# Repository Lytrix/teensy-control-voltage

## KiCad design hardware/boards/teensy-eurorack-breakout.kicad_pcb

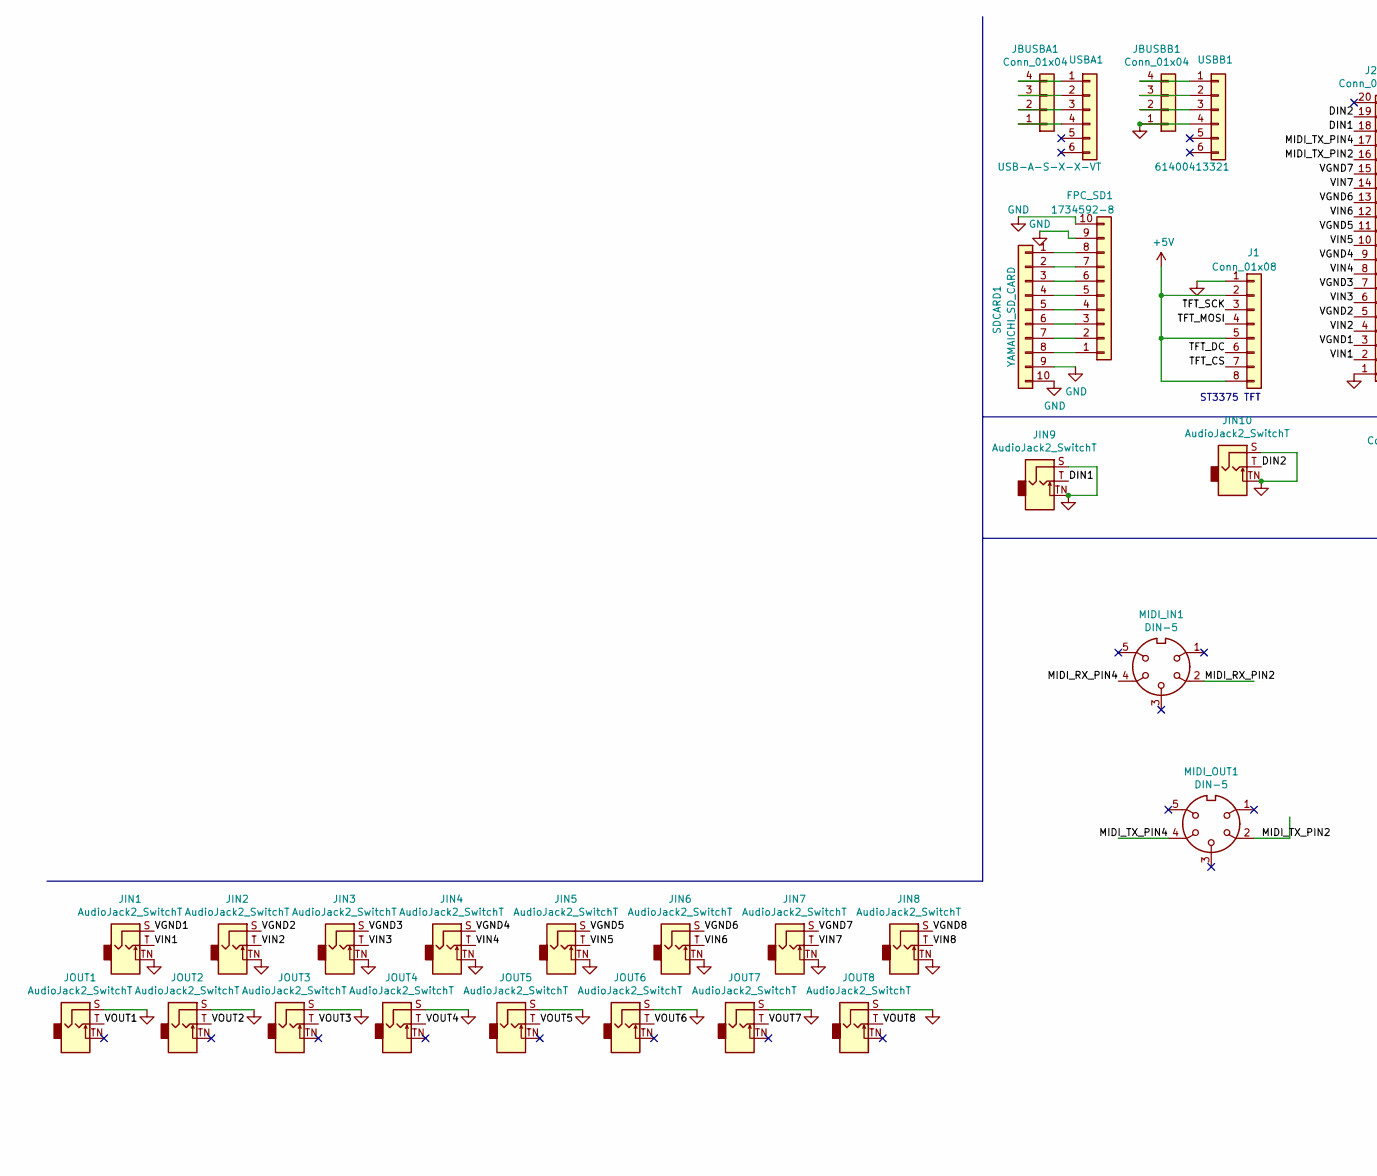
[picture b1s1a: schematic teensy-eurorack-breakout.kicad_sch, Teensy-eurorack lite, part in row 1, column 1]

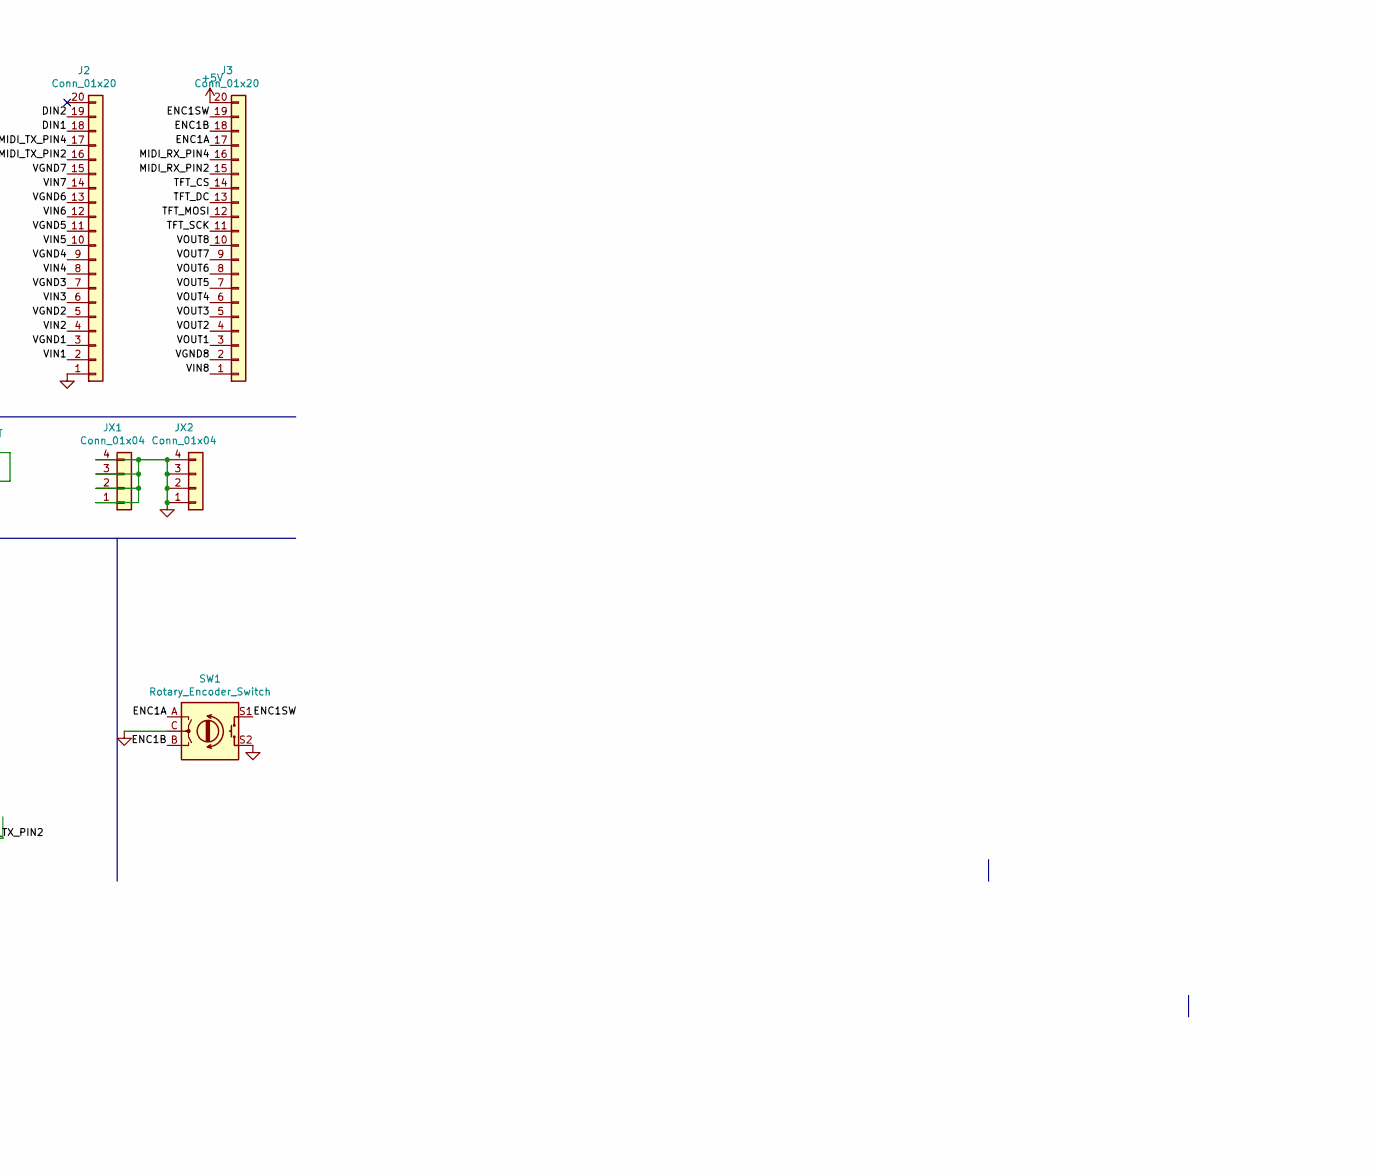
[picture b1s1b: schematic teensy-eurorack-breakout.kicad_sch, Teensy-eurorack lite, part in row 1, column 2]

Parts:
FPC_SD1: 1734592-8; HFW8R-1STE1LF
J1: Conn_01x08; ST7735
J2, J3: Conn_01x20; PinSocket_1x20_P2.54mm_Vertical
JBUSBA1: Conn_01x04; PinSocket_1x04_P2.54mm_Vertical
JBUSBB1: Conn_01x04; PinSocket_1x04_P2.54mm_Vertical
JIN1, JIN2, JIN3, JIN4, JIN5, JIN6, JIN7, JIN8, JIN9, JIN10: AudioJack2_SwitchT; WQP-PJ301M-12_JACK
JOUT1, JOUT2, JOUT3, JOUT4, JOUT5, JOUT6, JOUT7, JOUT8: AudioJack2_SwitchT; WQP-PJ301M-12_JACK
JX1, JX2: Conn_01x04; PinSocket_1x04_P2.54mm_Vertical
MIDI_IN1: DIN-5; OG-MIDI_SD-50BV
MIDI_OUT1: DIN-5; OG-MIDI_SD-50BV
SDCARD1: YAMAICHI_SD_CARD; YAMAICHI_MICROSD_VERTICAL
SW1: Rotary_Encoder_Switch; RotaryEncoder_Alps_EC12E-Switch_Vertical_H20mm_CircularMoun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
USBA1: USB-A-S-X-X-VT
USBB1: 61400413321; WURTH_ELECTRONICS_61400413321_0

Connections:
+5V: J1.2, J1.5, J1.8, J3.20
/DIN1: J2.18, JIN9.T
/DIN2: J2.19, JIN10.T
/ENC1A: J3.17, SW1.A
/ENC1B: J3.18, SW1.B
/ENC1SW: J3.19, SW1.S1
/MIDI_RX_PIN2: J3.15, MIDI_IN1.2
/MIDI_RX_PIN4: J3.16, MIDI_IN1.4
/MIDI_TX_PIN2: J2.16, MIDI_OUT1.2
/MIDI_TX_PIN4: J2.17, MIDI_OUT1.4
/TFT_CS: J1.7, J3.14
/TFT_DC: J1.6, J3.13
/TFT_MOSI: J1.4, J3.12
/TFT_SCK: J1.3, J3.11
/VGND1: J2.3, JIN1.S
/VGND2: J2.5, JIN2.S
/VGND3: J2.7, JIN3.S
/VGND4: J2.9, JIN4.S
/VGND5: J2.11, JIN5.S
/VGND6: J2.13, JIN6.S
/VGND7: J2.15, JIN7.S
/VGND8: J3.2, JIN8.S
/VIN1: J2.2, JIN1.T
/VIN2: J2.4, JIN2.T
/VIN3: J2.6, JIN3.T
/VIN4: J2.8, JIN4.T
/VIN5: J2.10, JIN5.T
/VIN6: J2.12, JIN6.T
/VIN7: J2.14, JIN7.T
/VIN8: J3.1, JIN8.T
/VOUT1: J3.3, JOUT1.T
/VOUT2: J3.4, JOUT2.T
/VOUT3: J3.5, JOUT3.T
/VOUT4: J3.6, JOUT4.T
/VOUT5: J3.7, JOUT5.T
/VOUT6: J3.8, JOUT6.T
/VOUT7: J3.9, JOUT7.T
/VOUT8: J3.10, JOUT8.T
GND: FPC_SD1.9, FPC_SD1.10, J1.1, J2.1, JBUSBB1.1, JIN1.TN, JIN2.TN, JIN3.TN, JIN4.TN, JIN5.TN, JIN6.TN, JIN7.TN, JIN8.TN, JIN9.S, JIN9.TN, JIN10.S, JIN10.TN, JOUT1.S, JOUT2.S, JOUT3.S, JOUT4.S, JOUT5.S, JOUT6.S, JOUT7.S, JOUT8.S, JX1.1, JX1.2, JX1.3, JX1.4, JX2.1, JX2.2, JX2.3, JX2.4, SDCARD1.9, SDCARD1.10, SW1.C, SW1.S2, USBB1.4
unnamed: FPC_SD1.1, SDCARD1.8
unnamed: FPC_SD1.2, SDCARD1.7
unnamed: FPC_SD1.3, SDCARD1.6
unnamed: FPC_SD1.4, SDCARD1.5
unnamed: FPC_SD1.5, SDCARD1.4
unnamed: FPC_SD1.6, SDCARD1.3
unnamed: FPC_SD1.7, SDCARD1.2
unnamed: FPC_SD1.8, SDCARD1.1
unnamed: JBUSBA1.1, USBA1.4
unnamed: JBUSBA1.2, USBA1.3
unnamed: JBUSBA1.3, USBA1.2
unnamed: JBUSBA1.4, USBA1.1
unnamed: JBUSBB1.2, USBB1.3
unnamed: JBUSBB1.3, USBB1.2
unnamed: JBUSBB1.4, USBB1.1

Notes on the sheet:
ST3375 TFT

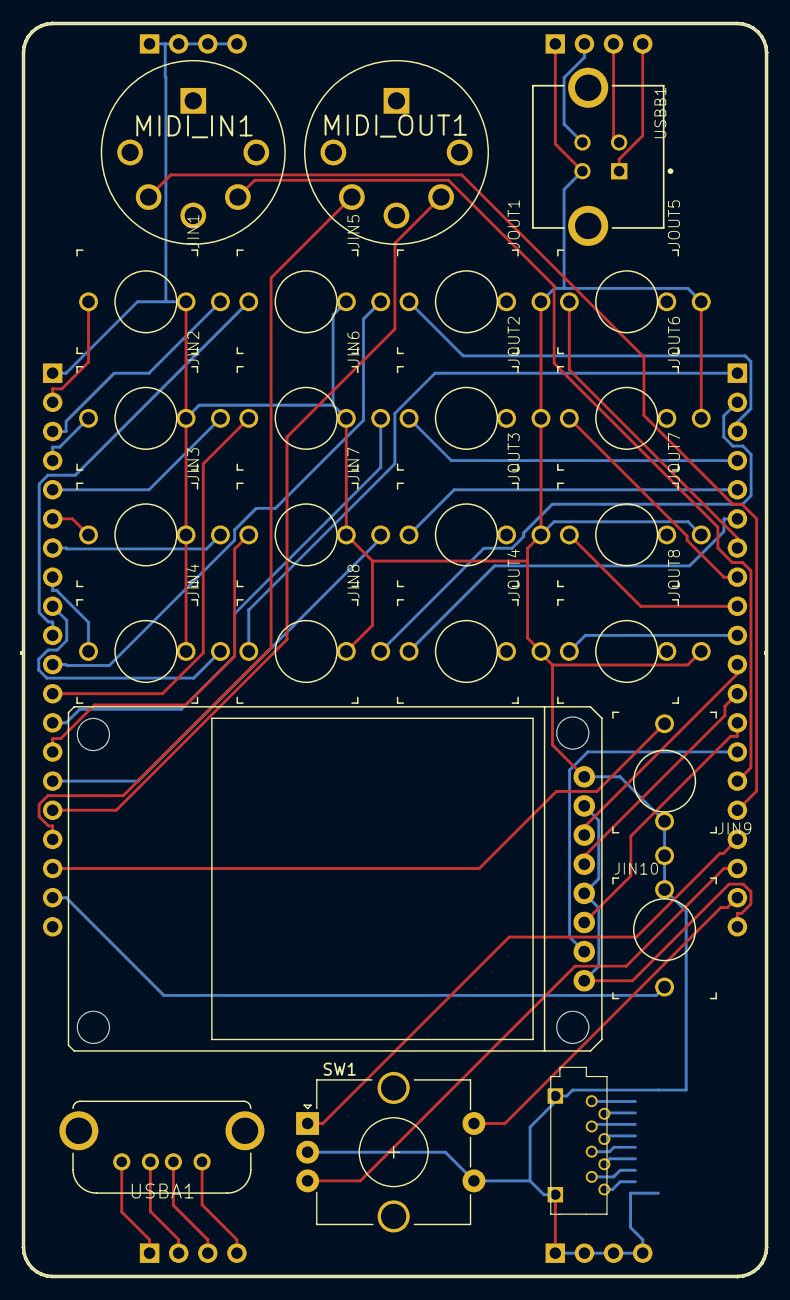
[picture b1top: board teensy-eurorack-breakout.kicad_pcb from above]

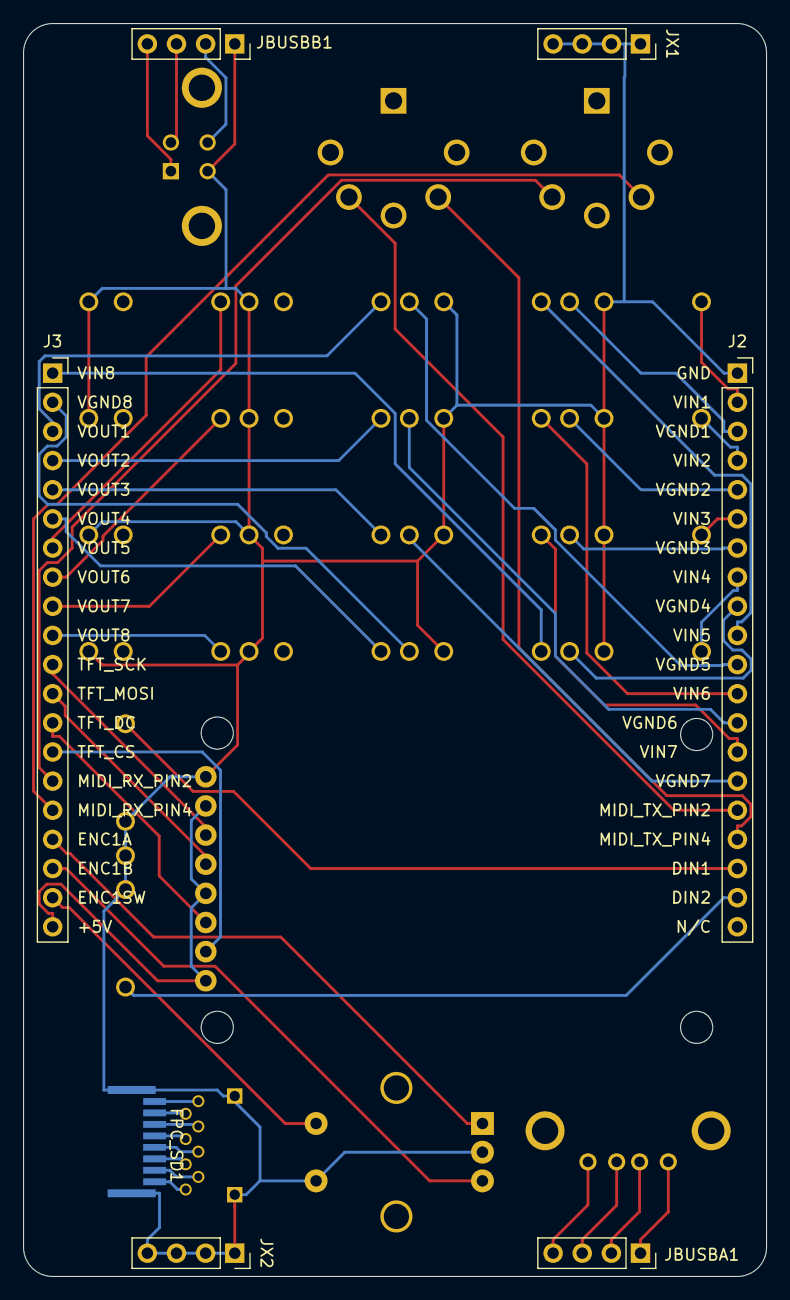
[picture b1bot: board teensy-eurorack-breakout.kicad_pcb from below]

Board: 2 copper layers, 64.8 x 109.2 mm, 32 parts (7 on the bottom side), 54 nets.

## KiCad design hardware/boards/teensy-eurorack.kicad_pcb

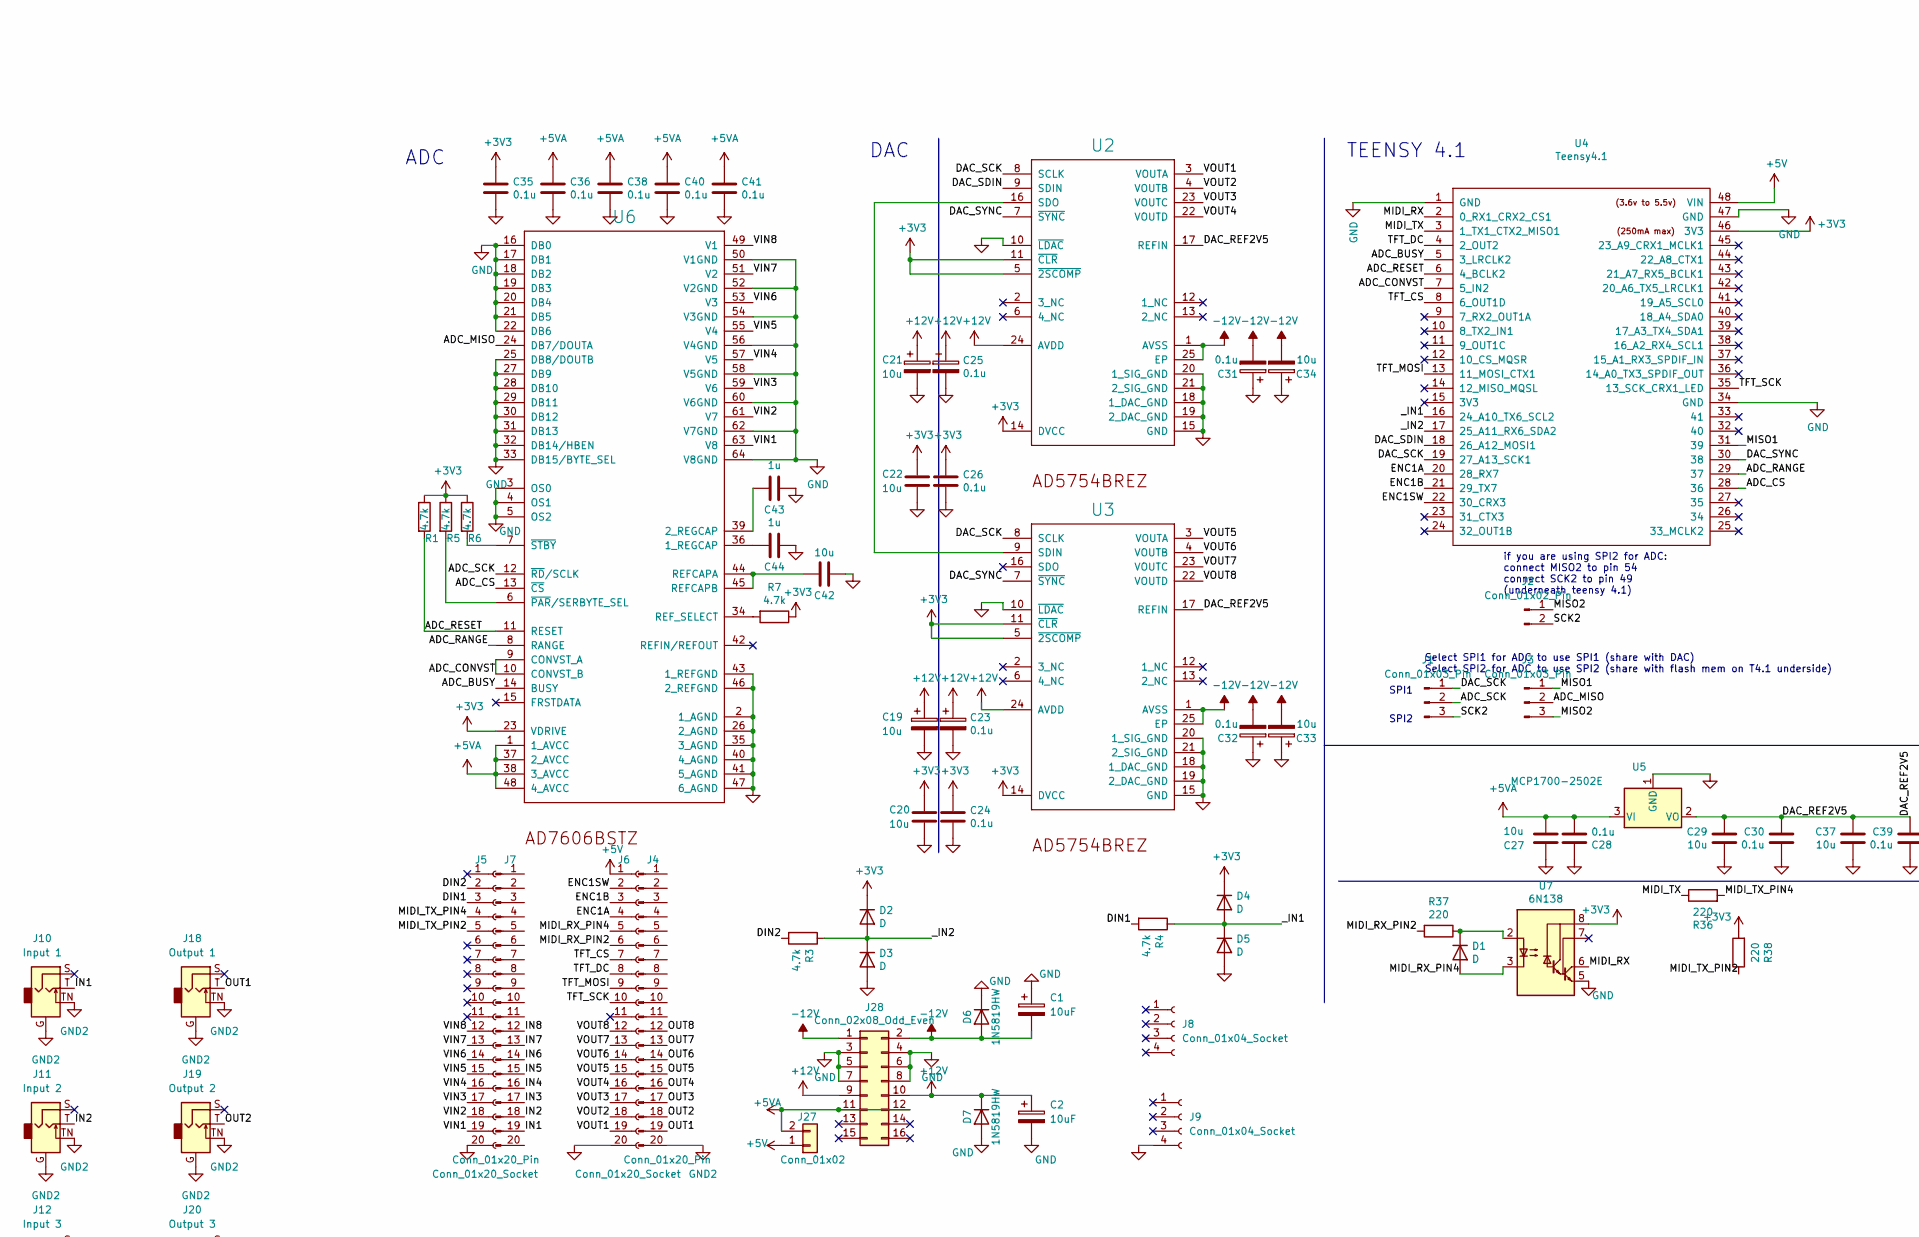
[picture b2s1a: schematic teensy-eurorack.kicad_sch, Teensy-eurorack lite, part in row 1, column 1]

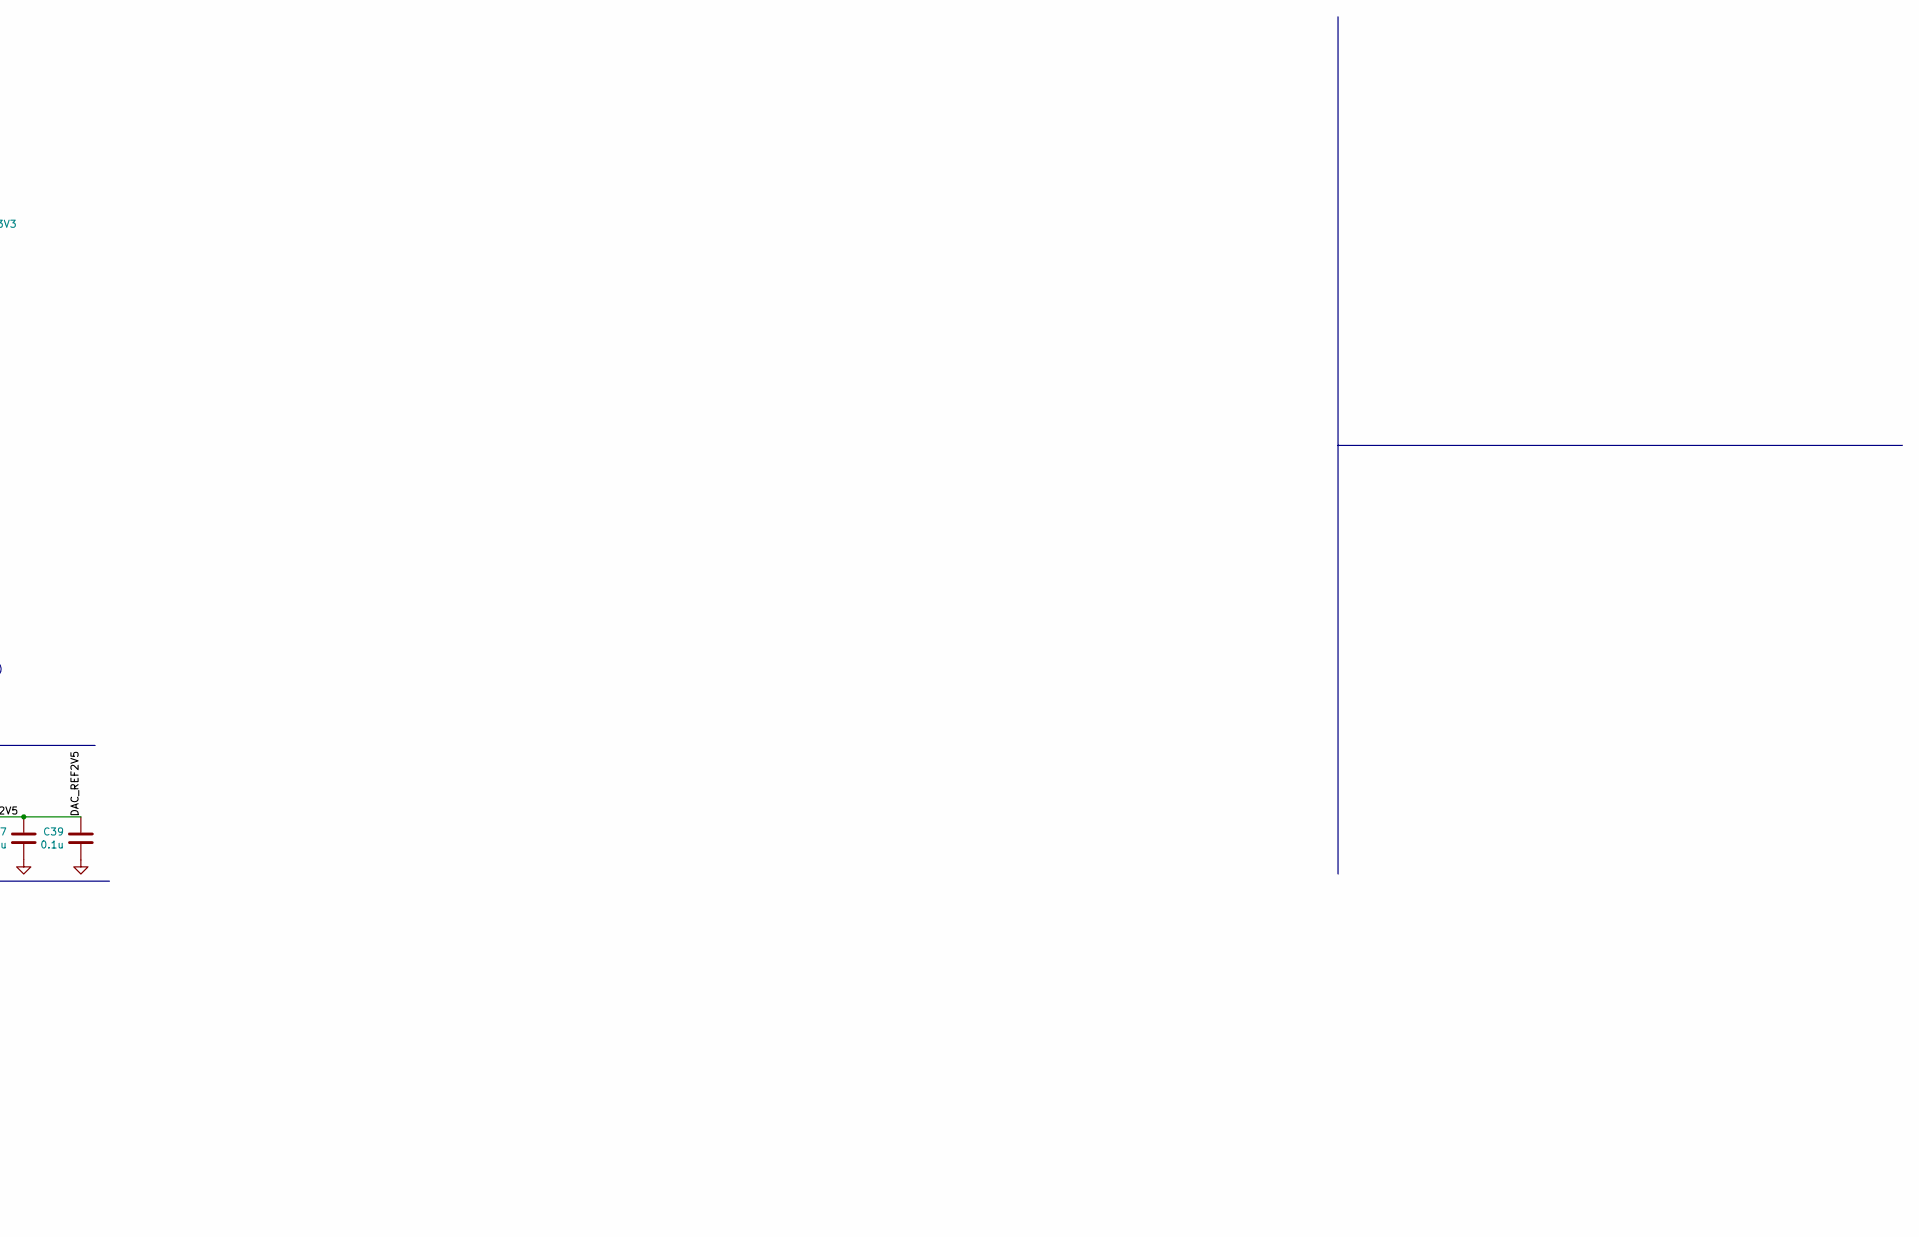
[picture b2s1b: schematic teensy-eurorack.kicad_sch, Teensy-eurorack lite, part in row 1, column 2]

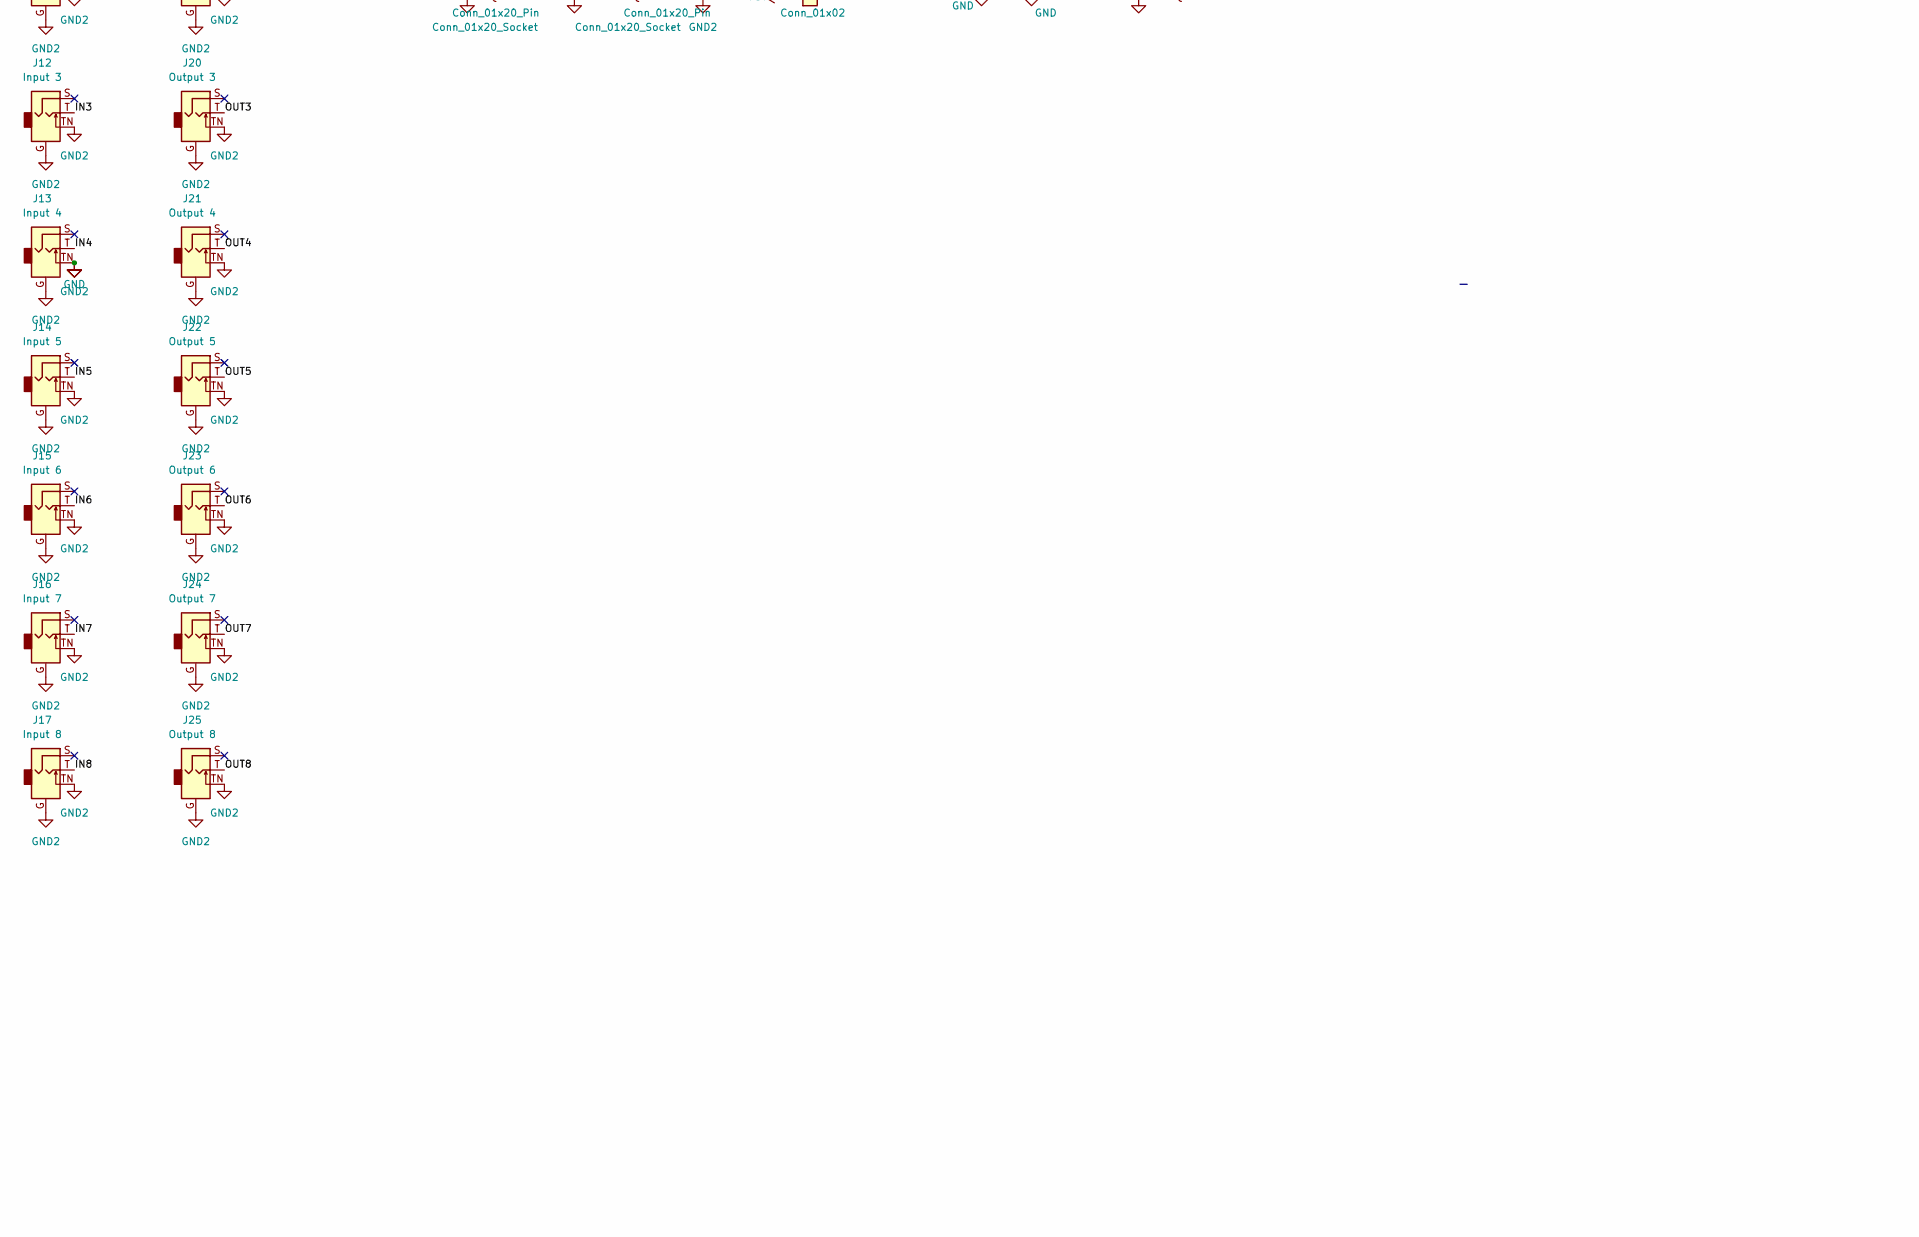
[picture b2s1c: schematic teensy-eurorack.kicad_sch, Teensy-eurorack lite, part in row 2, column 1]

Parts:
C1, C2: 10uF; CP_Elec_4x5.4
C19, C20, C21, C22, C27, C29, C33, C34, C37, C42: 10u; CP_EIA-3216-10_Kemet-I
C23, C24, C25, C26, C28, C30, C31, C32, C35, C36, C38, C39, C40, C41: 0.1u; C_0805_2012Metric
C43, C44: 1u; C_0805_2012Metric
D1, D2, D3, D4, D5: D; D_SOD-123
D6, D7: 1N5819HW; D_SOD-123
J1, J3: Conn_01x03_Pin; PinHeader_1x03_P2.54mm_Vertical
J2: Conn_01x02_Pin; PinHeader_1x02_P2.54mm_Vertical
J4, J7: Conn_01x20_Pin; PinHeader_1x20_P2.54mm_Vertical
J5, J6: Conn_01x20_Socket; PinSocket_1x20_P2.54mm_Vertical
J8, J9: Conn_01x04_Socket; PinHeader_1x04_P2.54mm_Vertical
J10: Input 1; Cliff_3.5mm_Stereo_Jack
J11: Input 2; Cliff_3.5mm_Stereo_Jack
J12: Input 3; Cliff_3.5mm_Stereo_Jack
J13: Input 4; Cliff_3.5mm_Stereo_Jack
J14: Input 5; Cliff_3.5mm_Stereo_Jack
J15: Input 6; Cliff_3.5mm_Stereo_Jack
J16: Input 7; Cliff_3.5mm_Stereo_Jack
J17: Input 8; Cliff_3.5mm_Stereo_Jack
J18: Output 1; Cliff_3.5mm_Stereo_Jack
J19: Output 2; Cliff_3.5mm_Stereo_Jack
J20: Output 3; Cliff_3.5mm_Stereo_Jack
J21: Output 4; Cliff_3.5mm_Stereo_Jack
J22: Output 5; Cliff_3.5mm_Stereo_Jack
J23: Output 6; Cliff_3.5mm_Stereo_Jack
J24: Output 7; Cliff_3.5mm_Stereo_Jack
J25: Output 8; Cliff_3.5mm_Stereo_Jack
J27: Conn_01x02; PinHeader_1x02_P2.54mm_Vertical
J28: Conn_02x08_Odd_Even; Eurorack_16_pin_header
R1, R3, R4, R5, R6, R7: 4.7k; R_0805_2012Metric
R36, R37, R38: 220; R_0805_2012Metric
U2, U3: AD5754BREZ; HTSSOP-24-1EP_4.4x7.8mm_P0.65mm_EP3.2x5mm
U4: Teensy4.1; Teensy41_tht
U5: MCP1700-2502E; SOT-23
U6: AD7606BSTZ; LQFP-64_10x10mm_P0.5mm
U7: 6N138; 6N138S

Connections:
+3V3: C20.1, C22.1, C24.1, C26.1, C35.1, D2.1 (K), D4.1 (K), R1.1, R5.1, R6.1, R7.1, R38.2, U2.5 (~2SCOMP), U2.11 (~CLR), U2.14 (DVCC), U3.5 (~2SCOMP), U3.11 (~CLR), U3.14 (DVCC), U4.46 (3V3), U6.23 (VDRIVE), U7.8 (VCC)
+5V: J6.1, J27.1, U4.48 (VIN)
+5VA: C27.2, C28.2, C36.1, C38.1, C40.1, C41.1, J27.2, J28.11, J28.12, U5.3 (VI), U6.1 (1_AVCC), U6.37 (2_AVCC), U6.38 (3_AVCC), U6.48 (4_AVCC)
+12V: C2.1, C19.1, C21.1, C23.1, C25.1, D7.1 (K), J28.9, J28.10, U2.24 (AVDD), U3.24 (AVDD)
-12V: C1.2, C31.2, C32.2, C33.2, C34.2, D6.2 (A), J28.1, J28.2, U2.1 (AVSS), U2.25 (EP), U3.1 (AVSS), U3.25 (EP)
/ADC_BUSY: U4.5 (3_LRCLK2), U6.14 (BUSY)
/ADC_CONVST: U4.7 (5_IN2), U6.9 (CONVST_A), U6.10 (CONVST_B)
/ADC_CS: U4.28 (36), U6.13 (~CS)
/ADC_MISO: J3.2, U6.24 (DB7/DOUTA)
/ADC_RANGE: U4.29 (37), U6.8 (RANGE)
/ADC_RESET: R1.2, U4.6 (4_BCLK2), U6.11 (RESET)
/ADC_SCK: J1.2, U6.12 (~RD/SCLK)
/DAC_REF2V5: C29.1, C30.1, C37.1, C39.1, U2.17 (REFIN), U3.17 (REFIN), U5.2 (VO)
/DAC_SCK: J1.1, U2.8 (SCLK), U3.8 (SCLK), U4.19 (27_A13_SCK1)
/DAC_SDIN: U2.9 (SDIN), U4.18 (26_A12_MOSI1)
/DAC_SYNC: U2.7 (~SYNC), U3.7 (~SYNC), U4.30 (38)
/DIN1: J5.3, R4.2
/DIN2: J5.2, R3.2
/ENC1A: J6.4, U4.20 (28_RX7)
/ENC1B: J6.3, U4.21 (29_TX7)
/ENC1SW: J6.2, U4.22 (30_CRX3)
/IN1: J7.19, J10.T
/IN2: J7.18, J11.T
/IN3: J7.17, J12.T
/IN4: J7.16, J13.T
/IN5: J7.15, J14.T
/IN6: J7.14, J15.T
/IN7: J7.13, J16.T
/IN8: J7.12, J17.T
/MIDI_RX: U4.2 (0_RX1_CRX2_CS1), U7.6 (VO2)
/MIDI_RX_PIN2: J6.6, R37.2
/MIDI_RX_PIN4: D1.2 (A), J6.5, U7.3 (C2)
/MIDI_TX: R36.1, U4.3 (1_TX1_CTX2_MISO1)
/MIDI_TX_PIN2: J5.5, R38.1
/MIDI_TX_PIN4: J5.4, R36.2
/MISO1: J3.1, U4.31 (39)
/MISO2: J2.1, J3.3
/OUT1: J4.19, J18.T
/OUT2: J4.18, J19.T
/OUT3: J4.17, J20.T
/OUT4: J4.16, J21.T
/OUT5: J4.15, J22.T
/OUT6: J4.14, J23.T
/OUT7: J4.13, J24.T
/OUT8: J4.12, J25.T
/SCK2: J1.3, J2.2
/TFT_CS: J6.7, U4.8 (6_OUT1D)
/TFT_DC: J6.8, U4.4 (2_OUT2)
/TFT_MOSI: J6.9, U4.13 (11_MOSI_CTX1)
/TFT_SCK: J6.10, U4.35 (13_SCK_CRX1_LED)
/VIN1: J5.19, U6.63 (V8)
/VIN2: J5.18, U6.61 (V7)
/VIN3: J5.17, U6.59 (V6)
/VIN4: J5.16, U6.57 (V5)
/VIN5: J5.15, U6.55 (V4)
/VIN6: J5.14, U6.53 (V3)
/VIN7: J5.13, U6.51 (V2)
/VIN8: J5.12, U6.49 (V1)
/VOUT1: J6.19, U2.3 (VOUTA)
/VOUT2: J6.18, U2.4 (VOUTB)
/VOUT3: J6.17, U2.23 (VOUTC)
/VOUT4: J6.16, U2.22 (VOUTD)
/VOUT5: J6.15, U3.3 (VOUTA)
/VOUT6: J6.14, U3.4 (VOUTB)
/VOUT7: J6.13, U3.23 (VOUTC)
/VOUT8: J6.12, U3.22 (VOUTD)
/_IN1: D4.2 (A), D5.1 (K), R4.1, U4.16 (24_A10_TX6_SCL2)
/_IN2: D2.2 (A), D3.1 (K), R3.1, U4.17 (25_A11_RX6_SDA2)
GND: C1.1, C2.2, C19.2, C20.2, C21.2, C22.2, C23.2, C24.2, C25.2, C26.2, C27.1, C28.1, C29.2, C30.2, C31.1, C32.1, C33.1, C34.1, C35.2, C36.2, C37.2, C38.2, C39.2, C40.2, C41.2, C42.1, C43.1, C44.1, D3.2 (A), D5.2 (A), D6.1 (K), D7.2 (A), J4.20, J5.20, J6.20, J9.4, J10.G, J10.TN, J11.G, J11.TN, J12.G, J12.TN, J13.G, J13.TN, J14.G, J14.TN, J15.G, J15.TN, J16.G, J16.TN, J17.G, J17.TN, J18.G, J18.TN, J19.G, J19.TN, J20.G, J20.TN, J21.G, J21.TN, J22.G, J22.TN, J23.G, J23.TN, J24.G, J24.TN, J25.G, J25.TN, J28.3, J28.4, J28.5, J28.6, J28.7, J28.8, U2.10 (~LDAC), U2.15 (GND), U2.18 (1_DAC_GND), U2.19 (2_DAC_GND), U2.20 (1_SIG_GND), U2.21 (2_SIG_GND), U3.10 (~LDAC), U3.15 (GND), U3.18 (1_DAC_GND), U3.19 (2_DAC_GND), U3.20 (1_SIG_GND), U3.21 (2_SIG_GND), U4.1 (GND), U4.34 (GND), U4.47 (GND), U5.1 (GND), U6.2 (1_AGND), U6.3 (OS0), U6.4 (OS1), U6.5 (OS2), U6.16 (DB0), U6.17 (DB1), U6.18 (DB2), U6.19 (DB3), U6.20 (DB4), U6.21 (DB5), U6.22 (DB6), U6.25 (DB8/DOUTB), U6.26 (2_AGND), U6.27 (DB9), U6.28 (DB10), U6.29 (DB11), U6.30 (DB12), U6.31 (DB13), U6.32 (DB14/HBEN), U6.33 (DB15/BYTE_SEL), U6.35 (3_AGND), U6.40 (4_AGND), U6.41 (5_AGND), U6.43 (1_REFGND), U6.46 (2_REFGND), U6.47 (6_AGND), U6.50 (V1GND), U6.52 (V2GND), U6.54 (V3GND), U6.56 (V4GND), U6.58 (V5GND), U6.60 (V6GND), U6.62 (V7GND), U6.64 (V8GND), U7.5 (GND)
unnamed: D1.1 (K), R37.1, U7.2 (C1)
unnamed: U2.16 (SDO), U3.9 (SDIN)
unnamed: C44.2, U6.36 (1_REGCAP)
unnamed: C43.2, U6.39 (2_REGCAP)
unnamed: C42.2, U6.44 (REFCAPA), U6.45 (REFCAPB)
unnamed: R7.2, U6.34 (REF_SELECT)
unnamed: R5.2, U6.6 (~PAR/SERBYTE_SEL)
unnamed: R6.2, U6.7 (~STBY)

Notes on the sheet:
ADC
DAC
SPI2
SPI1
if you are using SPI2 for ADC: connect MISO2 to pin 54 connect SCK2 to pin 49 (underneath teensy 4.1)
Select SPI1 for ADC to use SPI1 (share with DAC) Select SPI2 for ADC to use SPI2 (share with flash mem on T4.1 underside)
TEENSY 4.1

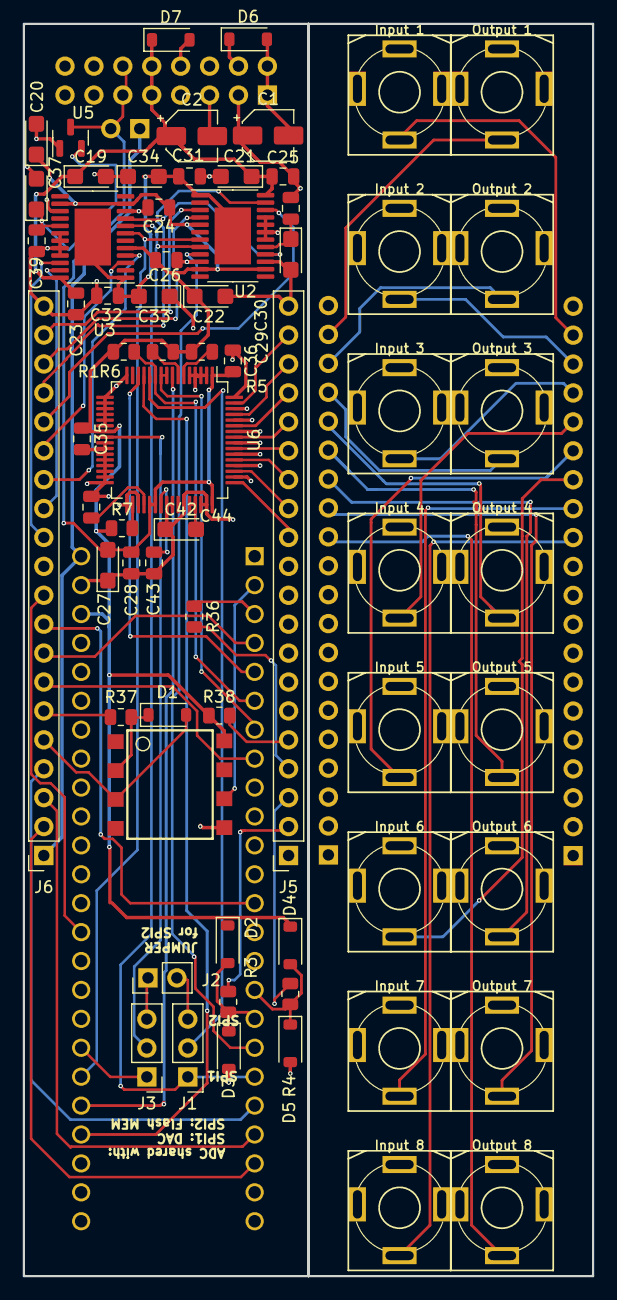
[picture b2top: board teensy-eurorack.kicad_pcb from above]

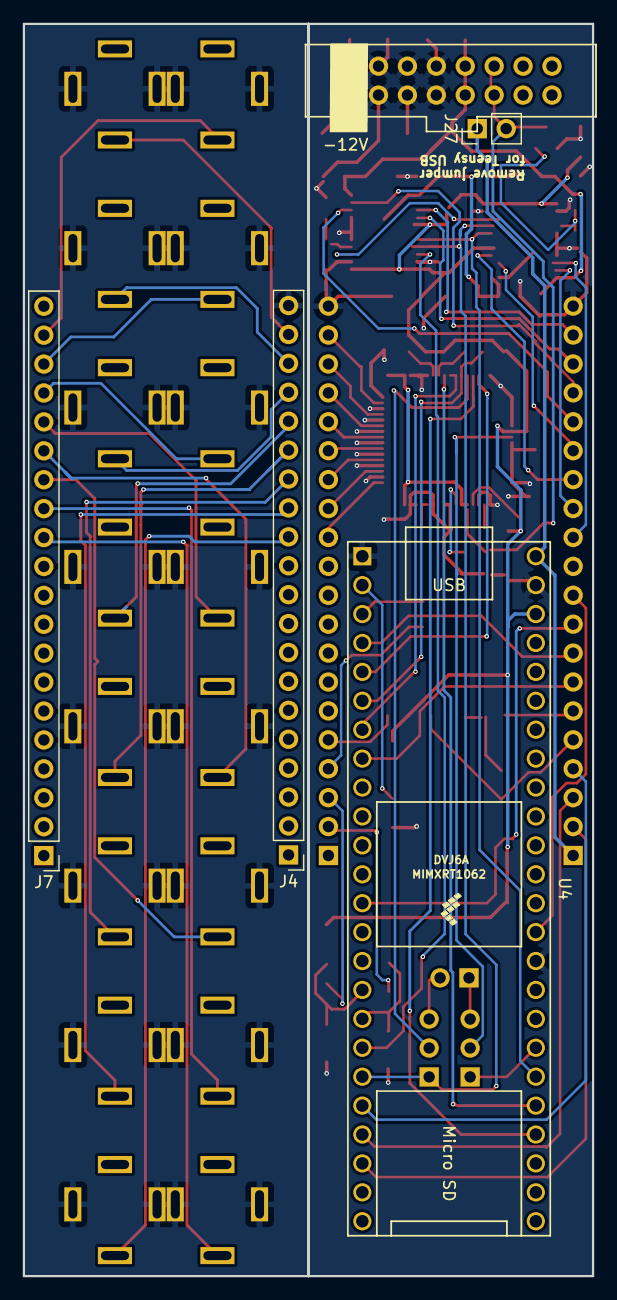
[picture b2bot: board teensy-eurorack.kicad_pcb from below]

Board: 2 copper layers, 50.0 x 110.0 mm, 72 parts (5 on the bottom side), 77 nets.

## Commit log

2024-05-27 Added jlcpcb parts and changed PCB to 10HP
